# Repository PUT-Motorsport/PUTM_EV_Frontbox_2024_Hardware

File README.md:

# PUTM_EV_Frontbox_2024_Hardware

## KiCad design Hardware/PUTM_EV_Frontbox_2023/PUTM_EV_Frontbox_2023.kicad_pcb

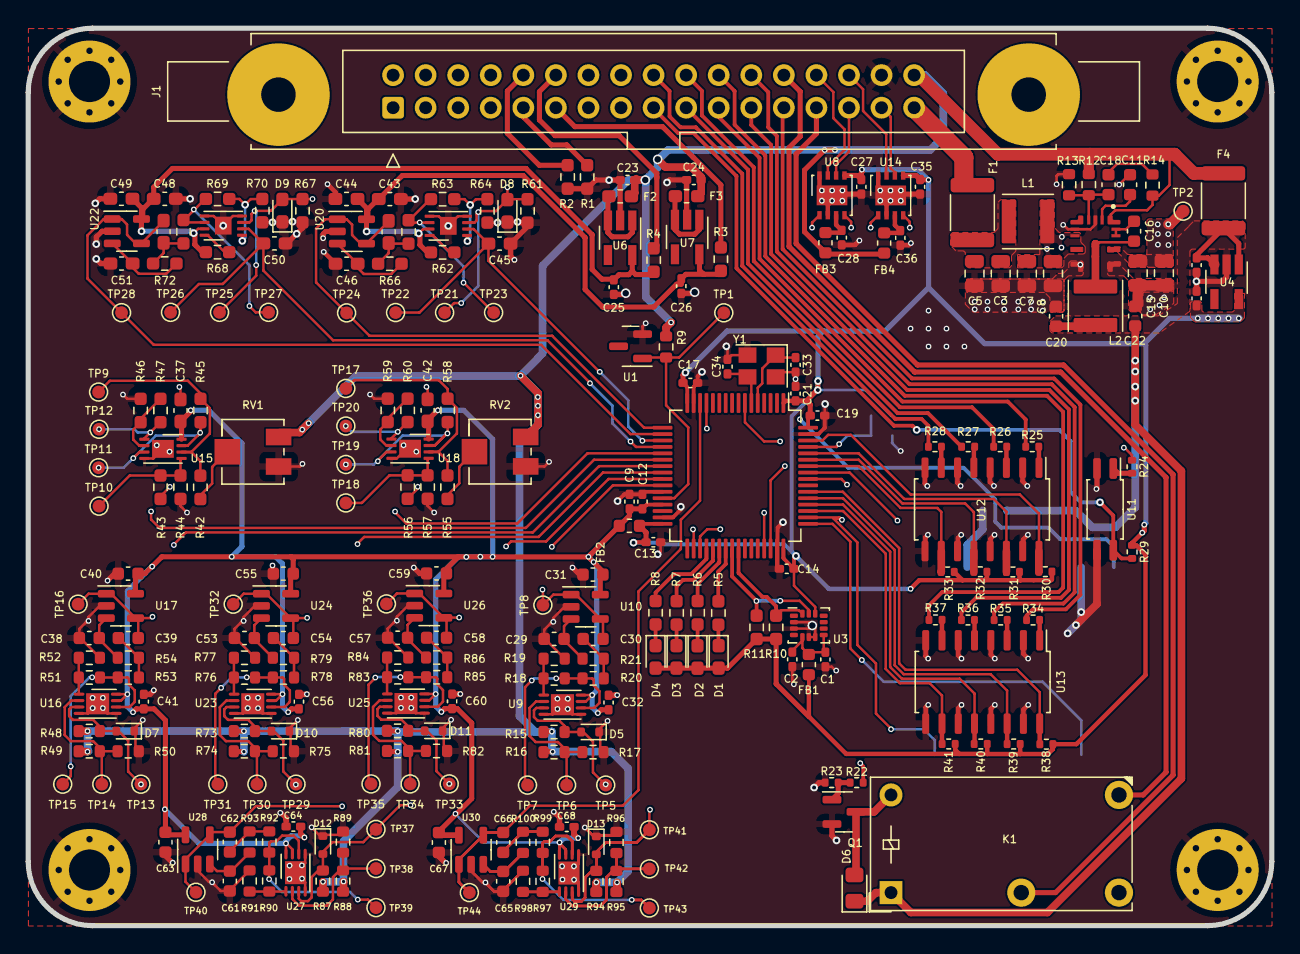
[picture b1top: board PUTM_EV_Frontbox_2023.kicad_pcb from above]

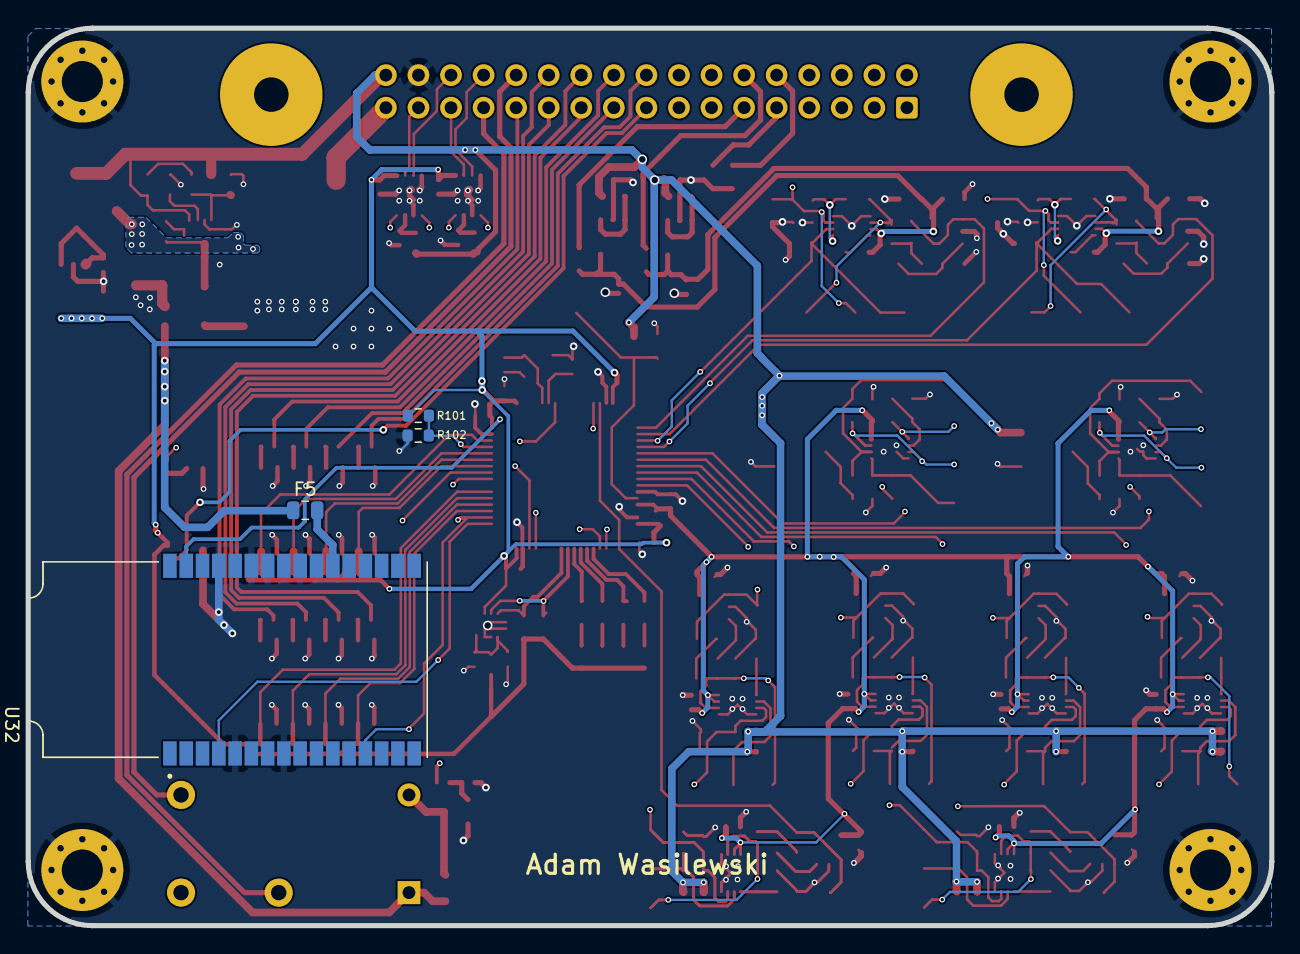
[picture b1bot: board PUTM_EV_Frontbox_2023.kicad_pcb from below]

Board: 4 copper layers, 97.0 x 70.0 mm, 277 parts (4 on the bottom side), 153 nets.

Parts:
C1, C2, C12, C13, C14, C17, C19, C21, C27, C28, C35, C36: 100nF; C_0402_1005Metric_Pad0.74x0.62mm_HandSolder
C3, C5: 2u2; C_0805_2012Metric
C4, C6, C9, C23, C24, C25, C26: 1uF; C_0402_1005Metric_Pad0.74x0.62mm_HandSolder
C7, C8: 4u7; C_0805_2012Metric
C10, C15: 220n; C_0805_2012Metric
C11: 1u; C_0603_1608Metric
C16, C29, C30, C31, C38, C39, C40, C53, C54, C55, C57, C58, C59, C61, C62, C63, C65, C66, C67: 100n; C_0603_1608Metric
C18: 22p; C_0603_1608Metric
C20, C22: 22u; C_0603_1608Metric
C32, C41, C56, C60, C64, C68: 100n; C_0402_1005Metric_Pad0.74x0.62mm_HandSolder
C33, C34: 10pF; C_0402_1005Metric_Pad0.74x0.62mm_HandSolder
C37, C42, C43, C44, C46, C47, C48, C49, C51, C52: 100n; C_0603_1608Metric_Pad1.08x0.95mm_HandSolder
C45, C50: 10n; C_0603_1608Metric_Pad1.08x0.95mm_HandSolder
D1, D2, D3, D4: LED; LED_0603_1608Metric_Pad1.05x0.95mm_HandSolder
D5, D7, D10, D11, D12, D13: 5V; D_SOD-523
D6: D_Small; D_0805_2012Metric_Pad1.15x1.40mm_HandSolder
D8, D9: 24V; D_0603_1608Metric_Pad1.05x0.95mm_HandSolder
F1, F4: 1.5A; Fuse_1812_4532Metric
F2, F3: 300mA; Fuse_0603_1608Metric_Pad1.05x0.95mm_HandSolder
F5: Fuse_Small; Fuse_0805_2012Metric
FB1, FB3, FB4: 60R@100MHz; L_0603_1608Metric
FB2: 1000Ω@100MHz; L_0603_1608Metric
H1, H2, H3, H4: MountingHole_Pad; MountingHole_3.2mm_M3_Pad_Via
J1: Conn_02x16_Counter_Clockwise; IDC-Header_2x17-1MP_P2.54mm_Latch6.5mm_Vertical
K1: FINDER-32.21-x000; Relay_SPDT_Finder_32.21-x000
L1, L2: 1u5; L_Abracon_ASPI-4030S
Q1: NX7002AK; SOT-23
R1, R2, R3, R4: 220R; R_0603_1608Metric_Pad0.98x0.95mm_HandSolder
R5, R6, R7, R8, R42, R44, R55, R57: 100R; R_0603_1608Metric_Pad0.98x0.95mm_HandSolder
R9, R14: 1k; R_0603_1608Metric
R10, R11: 10k; R_0603_1608Metric_Pad0.98x0.95mm_HandSolder
R12: 100k; R_0603_1608Metric
R13: 24k9; R_0603_1608Metric
R15, R16, R48, R49, R73, R74, R80, R81, R87, R88, R94, R95: 50k; R_0603_1608Metric
R17, R50, R75, R82, R89, R96: 5k; R_0603_1608Metric
R18, R19, R51, R52, R76, R77, R83, R84, R90, R91, R97, R98: TBD; R_0603_1608Metric
R20, R21, R53, R54, R78, R79, R85, R86, R92, R93, R99, R100: 3k3; R_0603_1608Metric
R22: 200R; R_0402_1005Metric
R23, R29, R30, R31, R32, R33, R38, R39, R40, R41: 10k; R_0402_1005Metric
R24, R25, R26, R27, R28, R34, R35, R36, R37: 2k; R_0402_1005Metric
R43, R45, R47, R56, R58, R60, R62, R68: 0R; R_0603_1608Metric_Pad0.98x0.95mm_HandSolder
R46, R59: 3k3; R_0603_1608Metric_Pad0.98x0.95mm_HandSolder
R61, R67: 100k; R_0603_1608Metric_Pad0.98x0.95mm_HandSolder
R63, R65, R66, R69, R71, R72: 4k7; R_0603_1608Metric_Pad0.98x0.95mm_HandSolder
R64, R70: 1k; R_0603_1608Metric_Pad0.98x0.95mm_HandSolder
R101, R102: 10k; R_0603_1608Metric
RV1, RV2: 2k; Potentiometer_Bourns_3214J_Horizontal
TP1, TP2, TP5, TP6, TP7, TP8, TP13, TP14, TP15, TP16, TP29, TP30, TP31, TP32, TP33, TP34, TP35, TP36, TP37, TP38, TP39, TP40, TP41, TP42, TP43, TP44: TestPoint_Small; TestPoint_Pad_D1.0mm
TP9, TP17: BR_N; TestPoint_Pad_D1.0mm
TP10, TP18: BR_P; TestPoint_Pad_D1.0mm
TP11, TP19: BR_MID; TestPoint_Pad_D1.0mm
TP12, TP20: BR_OUT; TestPoint_Pad_D1.0mm
TP21, TP25: APPS_P; TestPoint_Pad_D1.0mm
TP22, TP26: APPS_N; TestPoint_Pad_D1.0mm
TP23, TP27: APPS_MID; TestPoint_Pad_D1.0mm
TP24, TP28: APPS_OUT; TestPoint_Pad_D1.0mm
U1: LM4040C33FTA; SOT-23
U2: STM32G473RCTx; LQFP-64_10x10mm_P0.5mm
U3: IMS330DHCX; LGA-14_3x2.5mm_P0.5mm_LayoutBorder3x4y
U4, U6, U7: TLV743P; SOT-23-5_HandSoldering
U5: LM62440-Q1; IC_LM61460AANRJRR
U8, U14: MCP2542FDxMF; DFN-8-1EP_3x3mm_P0.65mm_EP1.55x2.4mm
U9, U16, U23, U25, U27, U29: MCP6N11-005; TDFN-8-1EP_3x2mm_P0.5mm_EP1.80x1.65mm
U10, U17, U20, U22, U24, U26, U28, U30: MCP6001; SOT-23-5
U11: FODM217B; SOP-4_4.4x2.6mm_P1.27mm
U12, U13: TLP291-4; SOIC-16_4.55x10.3mm_P1.27mm
U15, U18: MCP6002-xMC; DFN-8-1EP_3x2mm_P0.5mm_EP1.7x1.4mm
U19, U21: MCP6N11-005; TDFN-8-1EP_3x2mm_P0.5mm_EP1.3x1.4mm
U32: STLINK-V3MODS; MODULE_STLINK-V3MODS
Y1: ABM8G-48.000MHZ; Crystal_SMD_Abracon_ABM8G-4Pin_3.2x2.5mm

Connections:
+3.3V: C6.1, C13.1, C14.1, C17.1, C19.1, C21.1, C27.1, C35.1, D1.2 (A), D2.2 (A), D3.2 (A), D4.2 (A), FB1.1, FB2.1, R10.1, R11.1, R29.1, R30.1, R31.1, R32.1, R33.1, R38.1, R39.1, R40.1, R41.1, R101.1, U2.1 (VBAT), U2.16 (VDD), U2.32 (VDD), U2.48 (VDD), U2.64 (VDD), U3.12 (CS), U4.5 (OUT), U8.5 (VIO), U14.5 (VIO)
+3.3VA: C9.1, C12.1, C31.1, C32.1, C37.1, C40.1, C41.1, C42.1, C55.1, C56.1, C59.1, C60.1, C63.1, C64.1, C67.1, C68.1, FB2.2, U2.29 (VDDA), U9.7 (V+), U9.8 (EN), U10.5 (V+), U15.8 (V+), U16.7 (V+), U16.8 (EN), U17.5 (V+), U18.8 (V+), U23.7 (V+), U23.8 (EN), U24.5 (V+), U25.7 (V+), U25.8 (EN), U26.5 (V+), U27.7 (V+), U27.8 (EN), U28.5 (V+), U29.7 (V+), U29.8 (EN), U30.5 (V+)
+5V: C4.1, C20.1, C22.1, C23.1, C24.1, D6.1 (K), F2.1, F3.1, F4.1, F4.2, F5.1, FB3.1, FB4.1, J1.34, K1.A1, L2.2, R9.1, R12.1, R14.1, R15.1, R16.1, R48.1, R49.1, R73.1, R74.1, R80.1, R81.1, R87.1, R88.1, R94.1, R95.1, RV1.1, RV2.1, U4.1 (IN), U4.3 (EN), U5.1 (BIAS)
+24V: F1.1, J1.33
/APPS1_3V3: C25.1, C48.1, C49.1, R4.1, R68.2, U6.5 (OUT), U21.7 (V+), U22.5 (V+)
/APPS1_SHIFTED_3V3: J1.11, R3.2
/APPS1_SHIFTED_GND: J1.9, R1.2
/APPS2_3V3: C26.1, C43.1, C44.1, R3.1, R62.2, U7.5 (OUT), U19.7 (V+), U20.5 (V+)
/APPS2_SHIFTED_3V3: J1.12, R4.2
/APPS2_SHIFTED_GND: J1.10, R2.2
/APPS_POT_1: D9.2 (A2), J1.2, R67.1, TP25.1, U21.3 (+)
/APPS_POT_2: D8.2 (A2), J1.1, R61.1, TP21.1, U19.3 (+)
/APPS_sig1: C52.2, TP28.1, U2.18 (PA4), U22.1, U22.4 (-)
/APPS_sig2: C47.2, TP24.1, U2.17 (PA3), U20.1, U20.4 (-)
/BRAKE_POSITION_IN: D5.2 (A2), J1.7, R15.2, TP5.1, U9.3 (+)
/BRAKE_POSITION_OUT: C30.2, TP8.1, U2.26 (PB2), U10.1, U10.4 (-)
/BRAKE_PRESSURE1_IN: J1.3, R43.2
/BRAKE_PRESSURE2_IN: J1.8, R56.2
/BRAKE_PRESSURE_FRONT_OUT: R47.1, TP12.1, U2.22 (PC4), U15.1
/BRAKE_PRESSURE_REAR_OUT: R60.1, TP20.1, U2.21 (PA7), U18.1
/BSPD_SENSE: J1.21, R25.1
/Brake Position/IN+: R16.2, R17.1, TP6.1, U9.2 (-)
/CAN1+: J1.28, U8.7 (CANH)
/CAN1-: J1.29, U8.6 (CANL)
/CAN1_RX: U2.45 (PA11), U8.4 (RXD)
/CAN1_TX: U2.46 (PA12), U8.1 (TXD)
/CAN2+: J1.30, U14.7 (CANH)
/CAN2-: J1.31, U14.6 (CANL)
/CAN2_RX: U2.34 (PB12), U14.4 (RXD)
/CAN2_TX: U2.35 (PB13), U14.1 (TXD)
/DAC1_REF: C50.1, TP26.1, U2.20 (PA6), U21.2 (-)
/DAC2_REF: C45.1, TP22.1, U2.19 (PA5), U19.2 (-)
/DEBUG_LED1: R5.2, U2.39 (PC7)
/DEBUG_LED2: R6.2, U2.38 (PC6)
/DEBUG_LED3: R7.2, U2.37 (PB15)
/DEBUG_LED4: R8.2, U2.36 (PB14)
/EBS_SAFETY: J1.23, R36.1
/GEARBOX_TEMP_1: C62.2, TP40.1, U2.13 (PA1), U28.1, U28.4 (-)
/GEARBOX_TEMP_2: C66.2, TP44.1, U2.14 (PA2), U30.1, U30.4 (-)
/Gearbox_Temp_sensor_1/IN+: R88.2, R89.1, TP38.1, U27.2 (-)
/Gearbox_Temp_sensor_2/IN+: R95.2, R96.1, TP42.1, U29.2 (-)
/HSE_IN: C33.1, U2.5 (PF0), Y1.1
/HSE_OUT: C34.1, U2.6 (PF1), Y1.3
/IMU_SCL: R11.2, U2.40 (PC8), U3.13 (SCL)
/IMU_SDA: R10.2, U2.41 (PC9), U3.14 (SDA)
/INERTIA: J1.22, R37.1
/KILL_KIERA: J1.25, R34.1
/KILL_LEWY: J1.24, R35.1
/KILL_PRAWY: J1.20, R26.1
/LEFT_WHEEL_SC: J1.17, R29.2, U11.4
/NRST: U2.7 (PG10), U32.31 (T_NRST)
/OVERTRAVEL: J1.19, R27.1
/PT100_1: D12.2 (A2), J1.14, R87.2, TP37.1, U27.3 (+)
/PT100_2: D13.2 (A2), J1.13, R94.2, TP41.1, U29.3 (+)
/Power section/+24V_FUSED: C3.1, C5.1, F1.2, L1.1
/Power section/FB: C18.2, R12.2, R13.1, U5.4 (FB)
/Power section/SW: C16.1, L2.1, U5.10 (SW)
/Power section/VIN: C7.1, C8.1, C10.1, C15.1, L1.2, TP2.1, U5.7 (EN), U5.8 (VIN1), U5.12 (VIN2)
/RIGHT_WHEEL_SC: J1.18, R28.1
/SAFE-IN: J1.27, K1.11
/SAFE-OUT: J1.26, K1.12
/STEERING_POSITION_IN: D10.2 (A2), J1.5, R73.2, TP29.1, U23.3 (+)
/STEERING_POSITION_OUT: C54.2, TP32.1, U2.24 (PB0), U24.1, U24.4 (-)
/SUSPENSION_POT1_IN: D7.2 (A2), J1.4, R48.2, TP13.1, U16.3 (+)
/SUSPENSION_POT2_IN: D11.2 (A2), J1.6, R80.2, TP33.1, U25.3 (+)
/SUSP_L_OUT: C39.2, TP16.1, U2.23 (PC5), U17.1, U17.4 (-)
/SUSP_R_OUT: C58.2, TP36.1, U2.25 (PB1), U26.1, U26.4 (-)
/SWCLK: U2.50 (PA14), U32.13 (T_JCLK/T_SWCLK)
/SWDIO: U2.49 (PA13), U32.4 (T_JTMS/T_SWDIO)
/Safety_control: R22.1, U2.56 (PB3)
/Sense_BSPD: R30.2, U2.62 (PB9), U12.16
/Sense_EBS: R40.2, U2.52 (PC10), U13.12
/Sense_Left_Wheel: R24.1, U2.57 (PB4)
/Sense_Right_Wheel: R33.2, U2.58 (PB5), U12.10
/Sense_driver: R38.2, U2.54 (PC12), U13.16
/Sense_inertia: R41.2, U2.51 (PA15), U13.10
/Sense_left: R39.2, U2.53 (PC11), U13.14
/Sense_overtravel: R32.2, U2.59 (PB6), U12.12
/Sense_right: R31.2, U2.60 (PB7), U12.14
/Steering Position/IN+: R74.2, R75.1, TP30.1, U23.2 (-)
/Suspension Potentiometer (Left)/IN+: R49.2, R50.1, TP14.1, U16.2 (-)
/Suspension Potentiometer (Right)/IN+: R81.2, R82.1, TP34.1, U25.2 (-)
/VREF: R9.2, TP1.1, U1.1 (K), U2.28 (VREF+)
GND: C1.2, C2.2, C3.2, C4.2, C5.2, C6.2, C7.2, C8.2, C9.2, C10.2, C11.2, C12.2, C13.2, C14.2, C15.2, C17.2, C19.2, C20.2, C21.2, C22.2, C23.2, C24.2, C25.2, C26.2, C27.2, C28.2, C29.2, C31.2, C32.2, C33.2, C34.2, C35.2, C36.2, C37.2, C38.2, C40.2, C41.2, C42.2, C43.2, C44.2, C45.2, C46.2, C48.2, C49.2, C50.2, C51.2, C53.2, C55.2, C56.2, C57.2, C59.2, C60.2, C61.2, C63.2, C64.2, C65.2, C67.2, C68.2, D5.1 (A1), D7.1 (A1), D8.1 (A1), D9.1 (A1), D10.1 (A1), D11.1 (A1), D12.1 (A1), D13.1 (A1), H1.1, H2.1, H3.1, H4.1, J1.32, Q1.2 (S), R1.1, R2.1, R13.2, R17.2, R19.1, R23.2, R44.1, R46.2, R50.2, R52.1, R57.1, R59.2, R61.2, R64.1, R67.2, R70.1, R75.2, R77.1, R82.2, R84.1, R89.2, R91.1, R96.2, R98.1, R102.2, RV1.3, RV2.3, U1.2 (A), U2.15 (VSS), U2.27 (VSSA), U2.31 (VSS), U2.47 (VSS), U2.63 (VSS), U3.2 (SDX), U3.3 (SCX), U3.6 (GND), U3.7 (GND), U4.2 (GND), U5.3 (AGND), U5.6 (MODE/SYNC), U5.9 (PGND1), U5.11 (PGND2), U6.2 (GND), U7.2 (GND), U8.2 (VSS), U8.8 (STBY), U8.9 (VSS), U9.4 (V-), U9.5 (RF), U9.9 (EP), U10.2 (V-), U11.2, U11.3, U12.2, U12.4, U12.6, U12.8, U12.9, U12.11, U12.13, U12.15, U13.2, U13.4, U13.6, U13.8, U13.9, U13.11, U13.13, U13.15, U14.2 (VSS), U14.8 (STBY), U14.9 (VSS), U15.4 (V-), U15.9 (V-), U16.4 (V-), U16.5 (RF), U16.9 (EP), U17.2 (V-), U18.4 (V-), U18.9 (V-), U19.4 (V-), U19.5 (RF), U19.9 (EP), U20.2 (V-), U21.4 (V-), U21.5 (RF), U21.9 (EP), U22.2 (V-), U23.4 (V-), U23.5 (RF), U23.9 (EP), U24.2 (V-), U25.4 (V-), U25.5 (RF), U25.9 (EP), U26.2 (V-), U27.4 (V-), U27.5 (RF), U27.9 (EP), U28.2 (V-), U29.4 (V-), U29.5 (RF), U29.9 (EP), U30.2 (V-), U32.5 (GNDDETECT), U32.8 (GND_2), U32.24 (GND), U32.26 (GND2), U32.27 (GND3), U32.29 (GND4), Y1.2, Y1.4
unnamed: C18.1, R14.2
unnamed: C30.1, R20.2, R21.1
unnamed: C39.1, R53.2, R54.1
unnamed: C47.1, R65.2, R66.1
unnamed: C52.1, R71.2, R72.1
unnamed: C54.1, R78.2, R79.1
unnamed: C58.1, R85.2, R86.1
unnamed: C62.1, R92.2, R93.1
unnamed: C66.1, R99.2, R100.1
unnamed: D1.1 (K), R5.1
unnamed: D2.1 (K), R6.1
unnamed: D3.1 (K), R7.1
unnamed: D4.1 (K), R8.1
unnamed: D6.2 (A), K1.A2, Q1.3 (D)
unnamed: Q1.1 (G), R22.2, R23.1
unnamed: R18.2, R20.1, TP7.1, U9.6
unnamed: R24.2, U11.1
unnamed: R25.2, U12.1
unnamed: R26.2, U12.3
unnamed: R27.2, U12.5
unnamed: R28.2, U12.7
unnamed: R34.2, U13.1
unnamed: R35.2, U13.3
unnamed: R36.2, U13.5
unnamed: R37.2, U13.7
unnamed: R42.2, RV1.2
unnamed: R51.2, R53.1, TP15.1, U16.6
unnamed: R55.2, RV2.2
unnamed: R63.2, R65.1, TP23.1, U19.6
unnamed: R69.2, R71.1, TP27.1, U21.6
unnamed: R76.2, R78.1, TP31.1, U23.6
unnamed: R83.2, R85.1, TP35.1, U25.6
unnamed: R90.2, R92.1, TP39.1, U27.6
unnamed: R97.2, R99.1, TP43.1, U29.6
unnamed: R101.2, R102.1, U2.61 (PB8)
unnamed: C1.1, C2.1, FB1.2, U3.5 (VDDIO), U3.8 (VDD)
unnamed: C16.2, U5.13 (RBOOT), U5.14 (CBOOT)
unnamed: C11.1, U5.2 (VCC)
unnamed: F2.2, U6.1 (IN), U6.3 (EN)
unnamed: F3.2, U7.1 (IN), U7.3 (EN)
unnamed: C28.1, FB3.2, U8.3 (VDD)
unnamed: R18.1, R19.2, U9.1 (FG)
unnamed: C29.1, R21.2, U10.3 (+)
unnamed: C36.1, FB4.2, U14.3 (VDD)
unnamed: R45.1, TP11.1, U15.3 (+), U15.7
unnamed: R46.1, R47.2, U15.2 (-)
unnamed: R43.1, R44.2, TP10.1, U15.5 (+)
unnamed: R42.1, R45.2, TP9.1, U15.6 (-)
unnamed: R51.1, R52.2, U16.1 (FG)
unnamed: C38.1, R54.2, U17.3 (+)
unnamed: R58.1, TP19.1, U18.3 (+), U18.7
unnamed: R59.1, R60.2, U18.2 (-)
unnamed: R56.1, R57.2, TP18.1, U18.5 (+)
unnamed: R55.1, R58.2, TP17.1, U18.6 (-)
unnamed: R62.1, U19.8 (EN)
unnamed: R63.1, R64.2, U19.1 (FG)
unnamed: C46.1, R66.2, U20.3 (+)
unnamed: R68.1, U21.8 (EN)
unnamed: R69.1, R70.2, U21.1 (FG)
unnamed: C51.1, R72.2, U22.3 (+)
unnamed: R76.1, R77.2, U23.1 (FG)
unnamed: C53.1, R79.2, U24.3 (+)
unnamed: R83.1, R84.2, U25.1 (FG)
unnamed: C57.1, R86.2, U26.3 (+)
unnamed: R90.1, R91.2, U27.1 (FG)
unnamed: C61.1, R93.2, U28.3 (+)
unnamed: R97.1, R98.2, U29.1 (FG)
unnamed: C65.1, R100.2, U30.3 (+)
unnamed: F5.2, U32.22 (5V_OPT)

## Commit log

2024-03-20 .gitignore update
2024-03-21 Free PB0-Boot pin
2024-03-22 Fixed production issues
2024-03-22 Fixed corners
